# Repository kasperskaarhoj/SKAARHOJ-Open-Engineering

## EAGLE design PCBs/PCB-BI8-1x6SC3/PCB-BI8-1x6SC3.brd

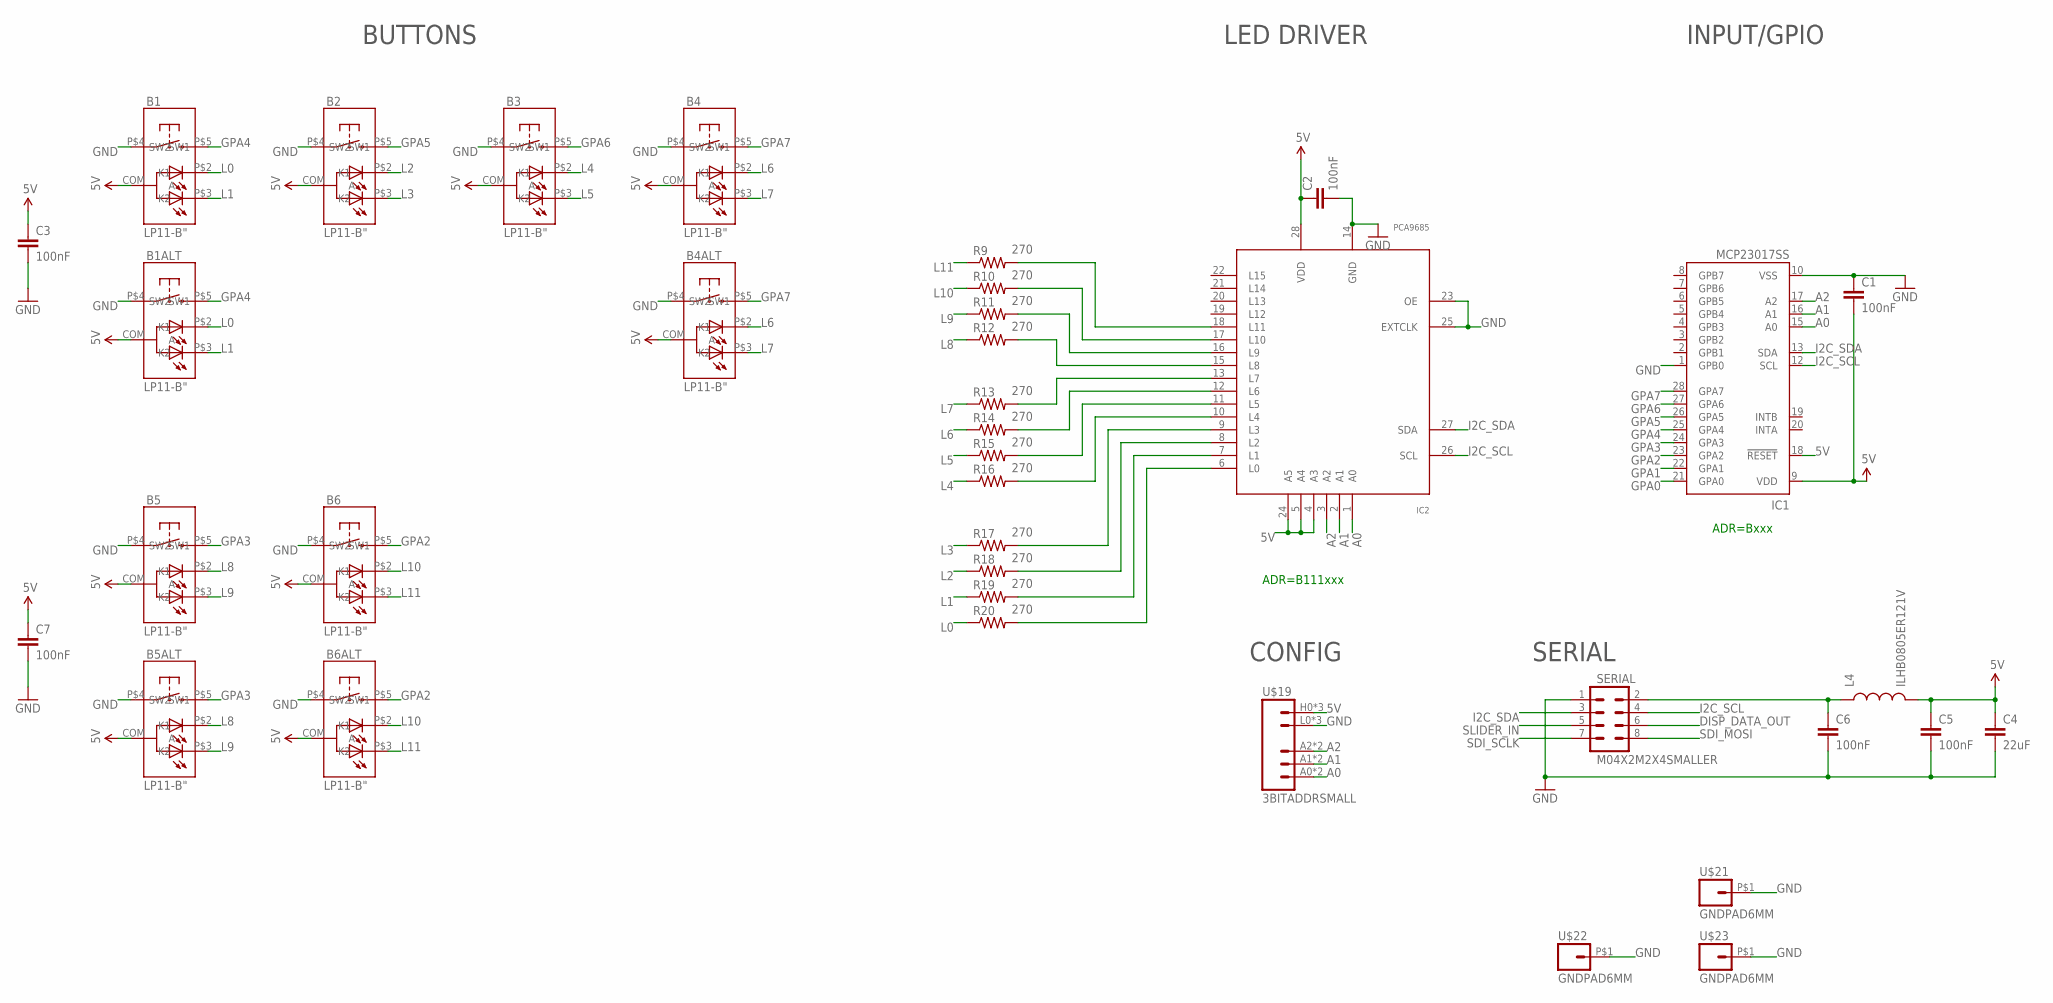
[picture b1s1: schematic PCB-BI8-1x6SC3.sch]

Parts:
B1, B1ALT, B2, B3, B4, B4ALT, B5, B5ALT, B6, B6ALT: LP11-B"; LP11
C1, C2, C3, C5, C6, C7: 100nF; 0603-CAP
C4: 22uF; 0805
IC1: MCP23017SS; SSOP28; MPN MCP23017-E/SS
IC2: PCA9685; TSSOP28
L4: ILHB0805ER121V; 0805
R9, R10, R11, R12, R13, R14, R15, R16, R17, R18, R19, R20: 270; 0603-RES
SERIAL: M04X2M2X4SMALLER; M2X4SMALLER
U$19: 3BITADDRSMALL; 3BITADDR_SMALL
U$21, U$22, U$23: GNDPAD6MM; 3.2MMPAD6MM

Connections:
5V: B1.COM (A), B1ALT.COM (A), B2.COM (A), B3.COM (A), B4.COM (A), B4ALT.COM (A), B5.COM (A), B5ALT.COM (A), B6.COM (A), B6ALT.COM (A), C1.2, C2.1, C3.1, C4.1, C5.1, C7.1, IC1.9 (VDD), IC1.18 (!RESET), IC2.4 (A3), IC2.5 (A4), IC2.24 (A5), IC2.28 (VDD), L4.2, U$19.H0 (VCC), U$19.H1 (VCC), U$19.H2 (VCC)
A0: IC1.15 (A0), IC2.1 (A0), U$19.A0, U$19.AS0 (A0)
A1: IC1.16 (A1), IC2.2 (A1), U$19.A1, U$19.AS1 (A1)
A2: IC1.17 (A2), IC2.3 (A2), U$19.A2, U$19.AS2 (A2)
DISP_DATA_OUT: SERIAL.6
GND: B1.P$4 (SW1), B1ALT.P$4 (SW1), B2.P$4 (SW1), B3.P$4 (SW1), B4.P$4 (SW1), B4ALT.P$4 (SW1), B5.P$4 (SW1), B5ALT.P$4 (SW1), B6.P$4 (SW1), B6ALT.P$4 (SW1), C1.1, C2.2, C3.2, C4.2, C5.2, C6.2, C7.2, IC1.1 (GPB0), IC1.10 (VSS), IC2.14 (GND), IC2.23 (OE), IC2.25 (EXTCLK), SERIAL.1, U$19.L0 (GND), U$19.L1 (GND), U$19.L2 (GND), U$21.P$1, U$22.P$1, U$23.P$1
GPA0: IC1.21 (GPA0)
GPA1: IC1.22 (GPA1)
GPA2: B6.P$5 (SW2), B6ALT.P$5 (SW2), IC1.23 (GPA2)
GPA3: B5.P$5 (SW2), B5ALT.P$5 (SW2), IC1.24 (GPA3)
GPA4: B1.P$5 (SW2), B1ALT.P$5 (SW2), IC1.25 (GPA4)
GPA5: B2.P$5 (SW2), IC1.26 (GPA5)
GPA6: B3.P$5 (SW2), IC1.27 (GPA6)
GPA7: B4.P$5 (SW2), B4ALT.P$5 (SW2), IC1.28 (GPA7)
I2C_SCL: IC1.12 (SCL), IC2.26 (SCL), SERIAL.4
I2C_SDA: IC1.13 (SDA), IC2.27 (SDA), SERIAL.3
L0: B1.P$2 (K1), B1ALT.P$2 (K1), R20.1
L1: B1.P$3 (K2), B1ALT.P$3 (K2), R19.1
L2: B2.P$2 (K1), R18.1
L3: B2.P$3 (K2), R17.1
L4: B3.P$2 (K1), R16.1
L5: B3.P$3 (K2), R15.1
L6: B4.P$2 (K1), B4ALT.P$2 (K1), R14.1
L7: B4.P$3 (K2), B4ALT.P$3 (K2), R13.1
L8: B5.P$2 (K1), B5ALT.P$2 (K1), R12.1
L9: B5.P$3 (K2), B5ALT.P$3 (K2), R11.1
L10: B6.P$2 (K1), B6ALT.P$2 (K1), R10.1
L11: B6.P$3 (K2), B6ALT.P$3 (K2), R9.1
unnamed: C6.1, L4.1, SERIAL.2
unnamed: IC2.13 (L7), R13.2
unnamed: IC2.12 (L6), R14.2
unnamed: IC2.11 (L5), R15.2
unnamed: IC2.10 (L4), R16.2
unnamed: IC2.9 (L3), R17.2
unnamed: IC2.8 (L2), R18.2
unnamed: IC2.7 (L1), R19.2
unnamed: IC2.6 (L0), R20.2
unnamed: IC2.15 (L8), R12.2
unnamed: IC2.16 (L9), R11.2
unnamed: IC2.17 (L10), R10.2
unnamed: IC2.18 (L11), R9.2
SDI_MOSI: SERIAL.8
SDI_SCLK: SERIAL.7
SLIDER_IN: SERIAL.5

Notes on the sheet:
ADR=B111xxx
ADR=Bxxx
BUTTONS
LED DRIVER
INPUT/GPIO
SERIAL
CONFIG

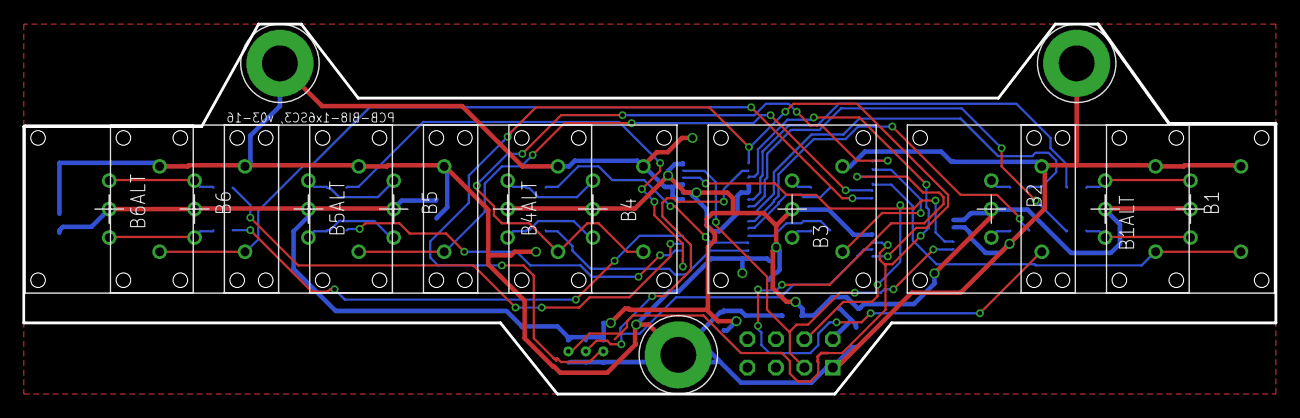
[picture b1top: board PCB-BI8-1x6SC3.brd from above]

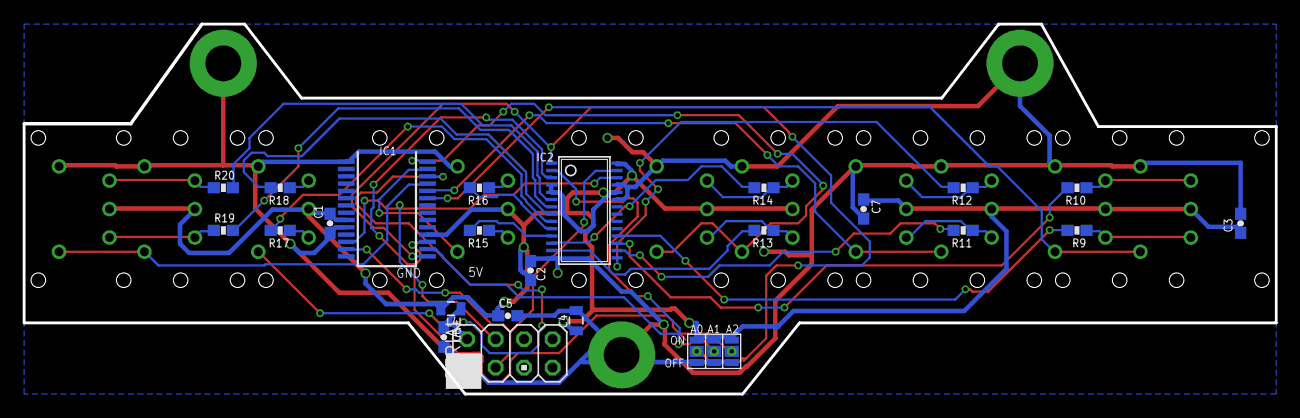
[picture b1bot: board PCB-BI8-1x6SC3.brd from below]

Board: 2 copper layers, 111.8 x 33.0 mm, 37 parts (24 on the bottom side), 38 nets.

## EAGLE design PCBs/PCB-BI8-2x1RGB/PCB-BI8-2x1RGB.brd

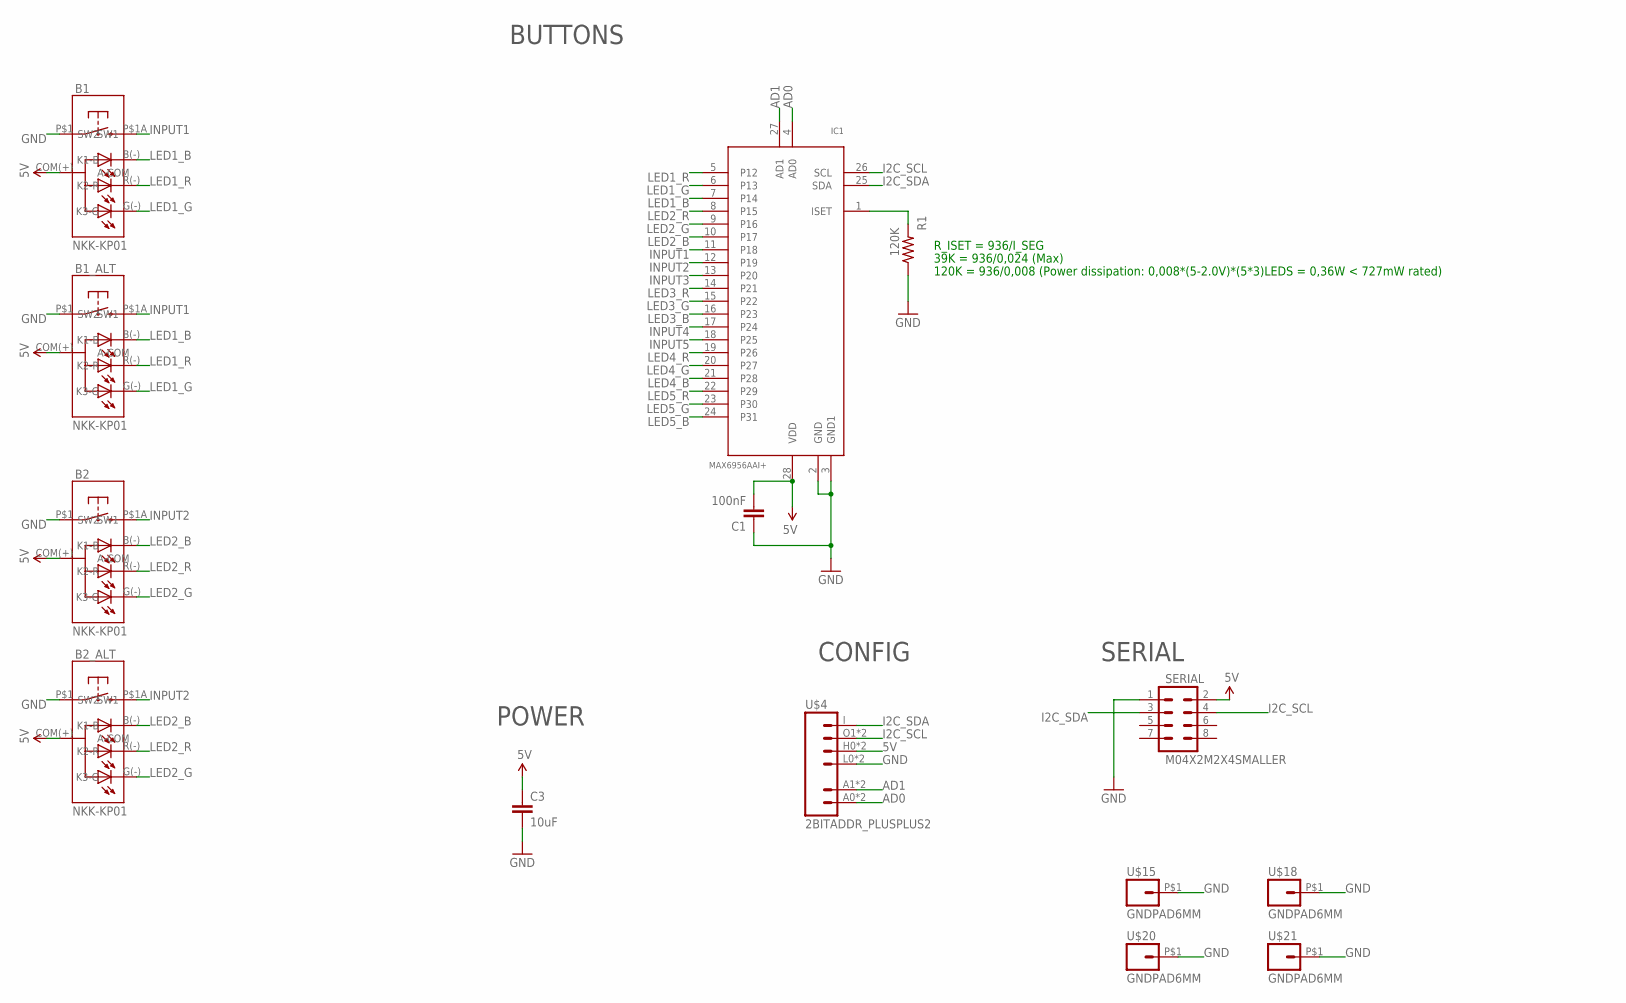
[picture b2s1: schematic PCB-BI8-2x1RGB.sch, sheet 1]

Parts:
B1, B1_ALT, B2, B2_ALT: NKK-KP01
C1: 100nF; 0603-CAP
C3: 10uF; 0805
IC1: MAX6956AAI+; SSOP28
R1: 120K; 0603-RES
SERIAL: M04X2M2X4SMALLER; M2X4SMALLER
U$4: 2BITADDR_PLUSPLUS2; 2BITADDR_SMALL_PLUS2
U$15, U$18, U$20, U$21: GNDPAD6MM; 3.2MMPAD6MM

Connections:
5V: B1.COM(+) (A-COM), B1_ALT.COM(+) (A-COM), B2.COM(+) (A-COM), B2_ALT.COM(+) (A-COM), C1.2, C3.1, IC1.28 (VDD), SERIAL.2, U$4.H0 (VCC), U$4.H1 (VCC)
AD0: IC1.4 (AD0), U$4.A0 (A1), U$4.AS0 (A1)
AD1: IC1.27 (AD1), U$4.A1 (A2), U$4.AS1 (A2)
GND: B1.P$1 (SW1), B1_ALT.P$1 (SW1), B2.P$1 (SW1), B2_ALT.P$1 (SW1), C1.1, C3.2, IC1.2 (GND), IC1.3 (GND1), R1.1, SERIAL.1, U$4.L0 (GND), U$4.L1 (GND), U$15.P$1, U$18.P$1, U$20.P$1, U$21.P$1
I2C_SCL: IC1.26 (SCL), SERIAL.4, U$4.O1 (3), U$4.O2 (3)
I2C_SDA: IC1.25 (SDA), SERIAL.3, U$4.I (4)
INPUT1: B1.P$1A (SW2), B1_ALT.P$1A (SW2), IC1.11 (P18)
INPUT2: B2.P$1A (SW2), B2_ALT.P$1A (SW2), IC1.12 (P19)
INPUT3: IC1.13 (P20)
INPUT4: IC1.17 (P24)
INPUT5: IC1.18 (P25)
LED1_B: B1.B(-) (K1-B), B1_ALT.B(-) (K1-B), IC1.7 (P14)
LED1_G: B1.G(-) (K3-G), B1_ALT.G(-) (K3-G), IC1.6 (P13)
LED1_R: B1.R(-) (K2-R), B1_ALT.R(-) (K2-R), IC1.5 (P12)
LED2_B: B2.B(-) (K1-B), B2_ALT.B(-) (K1-B), IC1.10 (P17)
LED2_G: B2.G(-) (K3-G), B2_ALT.G(-) (K3-G), IC1.9 (P16)
LED2_R: B2.R(-) (K2-R), B2_ALT.R(-) (K2-R), IC1.8 (P15)
LED3_B: IC1.16 (P23)
LED3_G: IC1.15 (P22)
LED3_R: IC1.14 (P21)
LED4_B: IC1.21 (P28)
LED4_G: IC1.20 (P27)
LED4_R: IC1.19 (P26)
LED5_B: IC1.24 (P31)
LED5_G: IC1.23 (P30)
LED5_R: IC1.22 (P29)
unnamed: IC1.1 (ISET), R1.2

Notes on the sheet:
BUTTONS
POWER
SERIAL
CONFIG
R_ISET = 936/I_SEG
39K = 936/0,024 (Max)
120K = 936/0,008 (Power dissipation: 0,008*(5-2.0V)*(5*3)LEDS = 0,36W < 727mW rated)

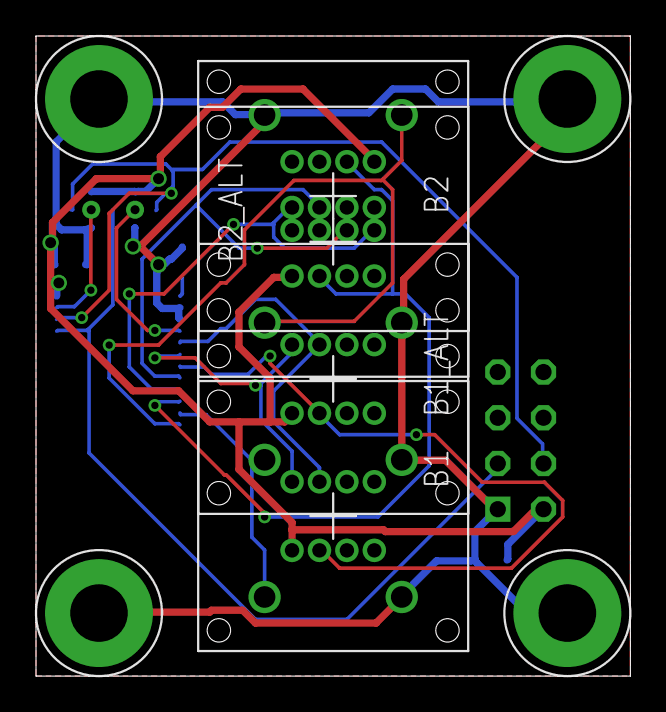
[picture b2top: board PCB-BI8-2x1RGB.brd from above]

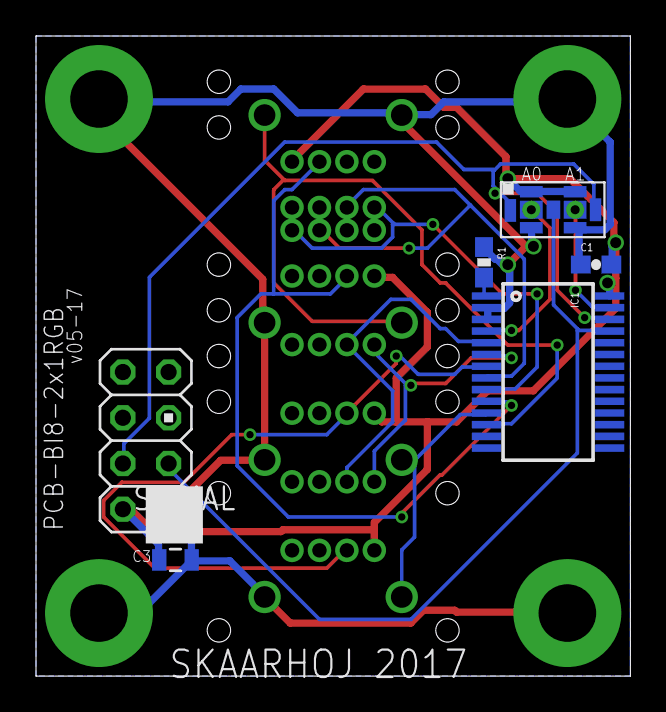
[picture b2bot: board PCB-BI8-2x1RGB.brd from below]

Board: 2 copper layers, 33.0 x 35.6 mm, 14 parts (6 on the bottom side), 15 nets.

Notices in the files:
parts and their libraries:
SparkFun: Licensing: CC v3.0 Share-Alike You are welcome to use this library for commercial purposes.
